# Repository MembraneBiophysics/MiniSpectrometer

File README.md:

# Mini Spectrometer

A low cost, low power, portable spectrometer for education and research.

For more information please see www.minispectrometer.co.uk

All the CAD files and code needed to make a range of different mini-spectrometers are included in the folders here. We'll be developing project instructions and information packs over the next little while but if you have any questions or would like any more information, please feel free to get in touch (contact details on the website link above).

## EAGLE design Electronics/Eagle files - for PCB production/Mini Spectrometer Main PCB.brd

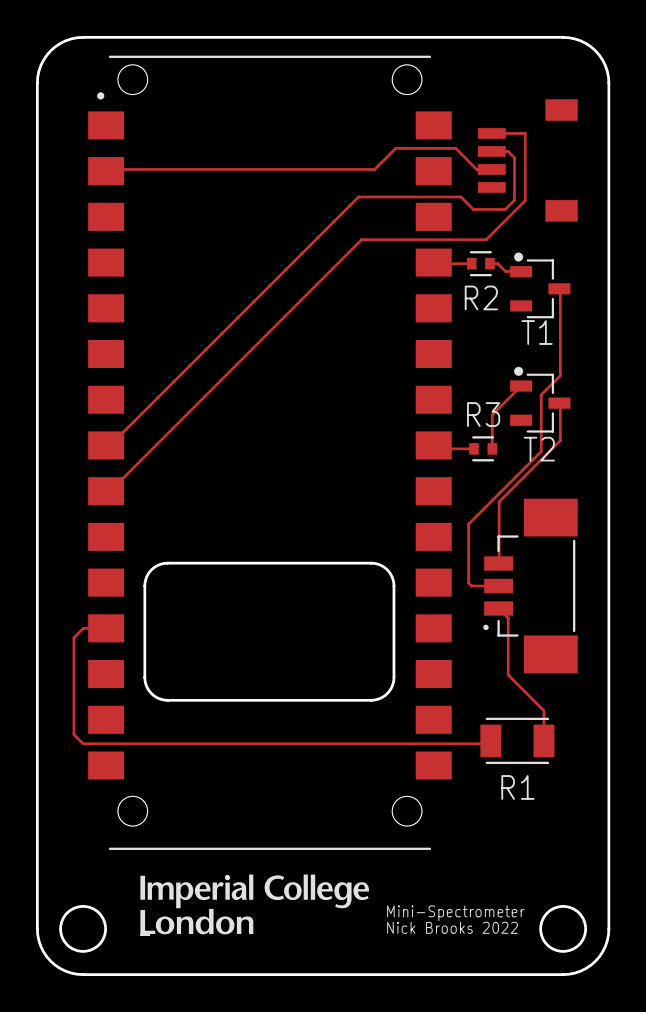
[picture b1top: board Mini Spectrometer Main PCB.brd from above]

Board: 2 copper layers, 31.8 x 52.1 mm, 8 parts (0 on the bottom side), 12 nets.

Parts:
J1: JST-SH-4WAY-2; JST_SM04B-SRSS-TB_LF__SN_
P1: 53261-0371; MOLEX_53261-0371
R1: 100; RESC3216X70
R2, R3: 1K; RESC1005X40
T1, T2: NPN; SOT95P237X112-3N
U1: ABX00027; MODULE_ABX00027

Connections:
GND: J1.1, T1.2, T2.2, U1.14, U1.19
unnamed: R1.1, U1.12
unnamed: R2.1, U1.27
unnamed: R3.1, U1.23
unnamed: R2.2, T1.1
unnamed: R3.2, T2.1
unnamed: J1.2, U1.2
unnamed: J1.3, U1.8
unnamed: J1.4, U1.9
unnamed: P1.1, R1.2
unnamed: P1.2, T1.3
unnamed: P1.3, T2.3

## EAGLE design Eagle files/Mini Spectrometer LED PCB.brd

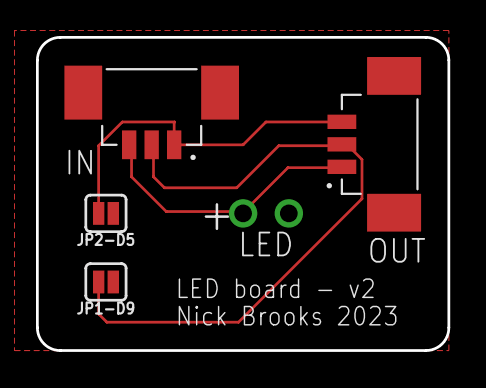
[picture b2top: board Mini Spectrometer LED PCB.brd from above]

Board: 2 copper layers, 22.9 x 17.4 mm, 5 parts (1 on the bottom side), 4 nets.

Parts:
IN: 53261-0371; MOLEX_53261-0371
JP1-D9, JP2-D5: JUMPER-SMT_2_NO_SILK; SMT-JUMPER_2_NO_SILK
LED: LED; LEDRD254W60D565H860B_W
OUT: 53261-0371; MOLEX_53261-0371

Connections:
GND: JP1-D9.1, JP2-D5.1, LED.2
unnamed: IN.3, LED.1, OUT.1
unnamed: IN.2, JP1-D9.2, OUT.2
unnamed: IN.1, JP2-D5.2, OUT.3

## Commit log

2023-10-04 Create file
2023-10-05 Upload of Arduino and Python code.

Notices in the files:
parts and their libraries:
SparkFun-Jumpers: Licensing: Creative Commons ShareAlike 4.0 International - https://creativecommons.org/licenses/by-sa/4.0
